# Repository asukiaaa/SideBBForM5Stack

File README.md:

# SideBBForM5Stack

An stack for M5Stack to use bread board easier.

# Where to buy

[SideBBForM5Stack - Switch Science](https://www.switch-science.com/catalog/4098/)

# License

MIT

# References

- [M5Stackの信号線をブレッドボードで扱いやすくするStackを作ってみた](https://asukiaaa.blogspot.com/2018/11/m5stacksidebb.html)
- [PartsandCircuits/M5Stack-3DPrintFiles](https://github.com/PartsandCircuits/M5Stack-3DPrintFiles)
- [DIY Mini Proto Board](http://forum.m5stack.com/topic/59/diy-mini-proto-board)

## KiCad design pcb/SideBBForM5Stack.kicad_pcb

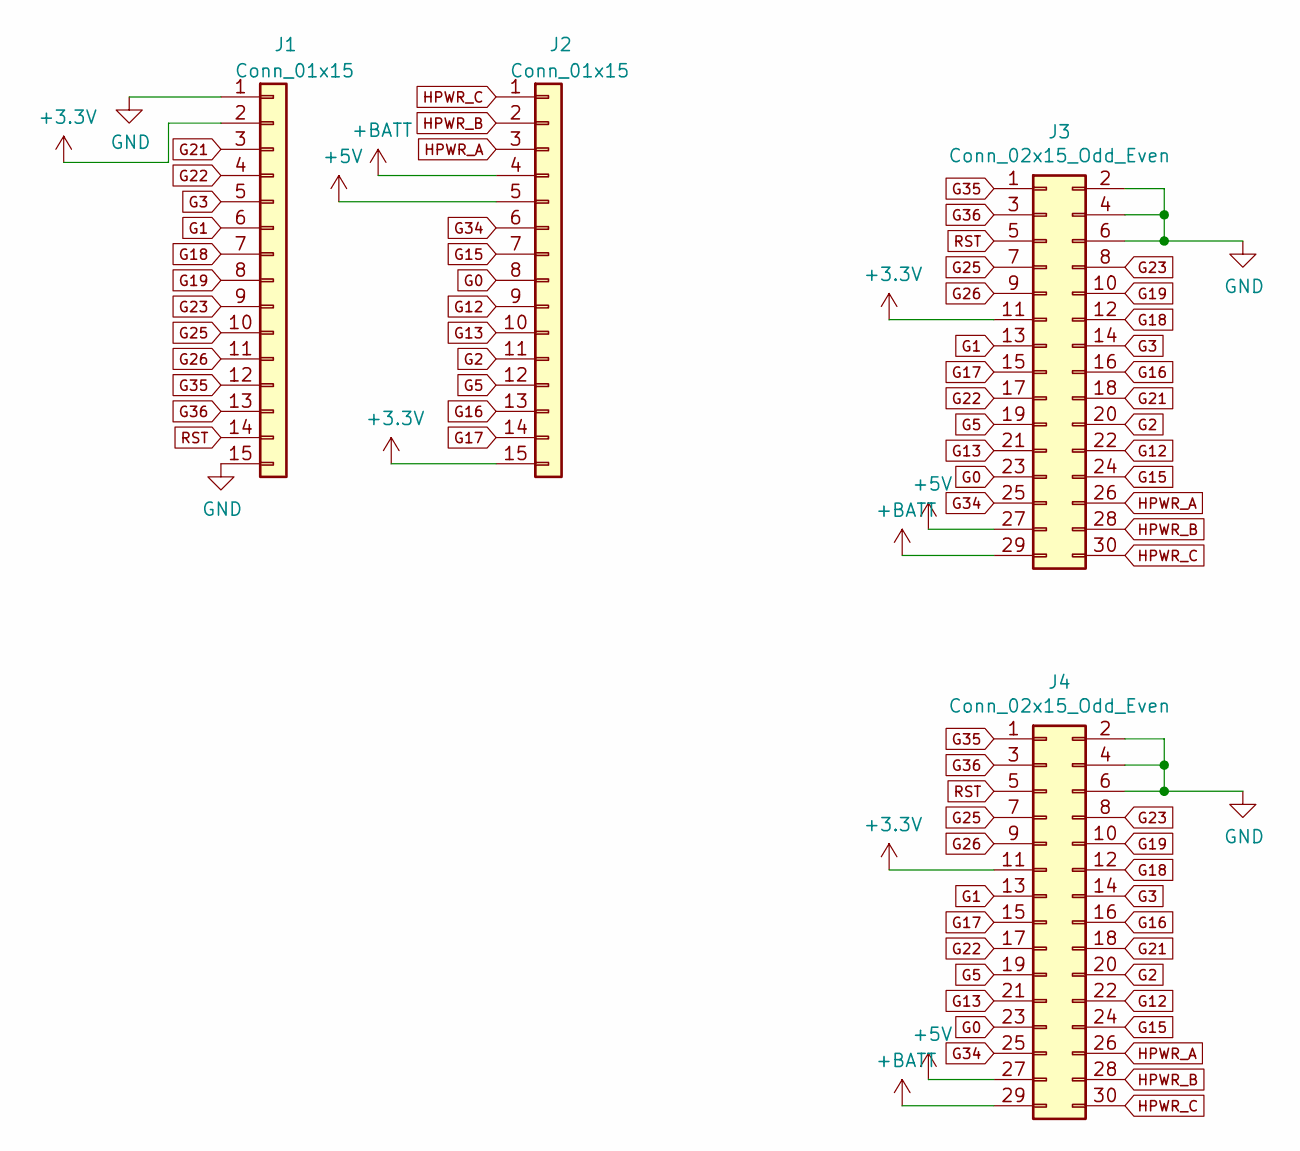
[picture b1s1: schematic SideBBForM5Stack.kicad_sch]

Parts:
J1, J2: Conn_01x15; PinSocket_1x15_P2.54mm_Vertical_without_silk
J3: Conn_02x15_Odd_Even; PinHeader_2x15_P2.54mm_M5Stack_SpacerPCB_pads
J4: Conn_02x15_Odd_Even; PinSocket_2x15_P2.54mm_Vertical_SMD_just_for_M5Stack_bottom

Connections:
+3V3: J1.2, J2.15, J3.11, J4.11
+5V: J2.5, J3.27, J4.27
+BATT: J2.4, J3.29, J4.29
G0: J2.8, J3.23, J4.23
G1: J1.6, J3.13, J4.13
G2: J2.11, J3.20, J4.20
G3: J1.5, J3.14, J4.14
G5: J2.12, J3.19, J4.19
G12: J2.9, J3.22, J4.22
G13: J2.10, J3.21, J4.21
G15: J2.7, J3.24, J4.24
G16: J2.13, J3.16, J4.16
G17: J2.14, J3.15, J4.15
G18: J1.7, J3.12, J4.12
G19: J1.8, J3.10, J4.10
G21: J1.3, J3.18, J4.18
G22: J1.4, J3.17, J4.17
G23: J1.9, J3.8, J4.8
G25: J1.10, J3.7, J4.7
G26: J1.11, J3.9, J4.9
G34: J2.6, J3.25, J4.25
G35: J1.12, J3.1, J4.1
G36: J1.13, J3.3, J4.3
GND: J1.1, J1.15, J3.2, J3.4, J3.6, J4.2, J4.4, J4.6
HPWR_A: J2.3, J3.26, J4.26
HPWR_B: J2.2, J3.28, J4.28
HPWR_C: J2.1, J3.30, J4.30
RST: J1.14, J3.5, J4.5

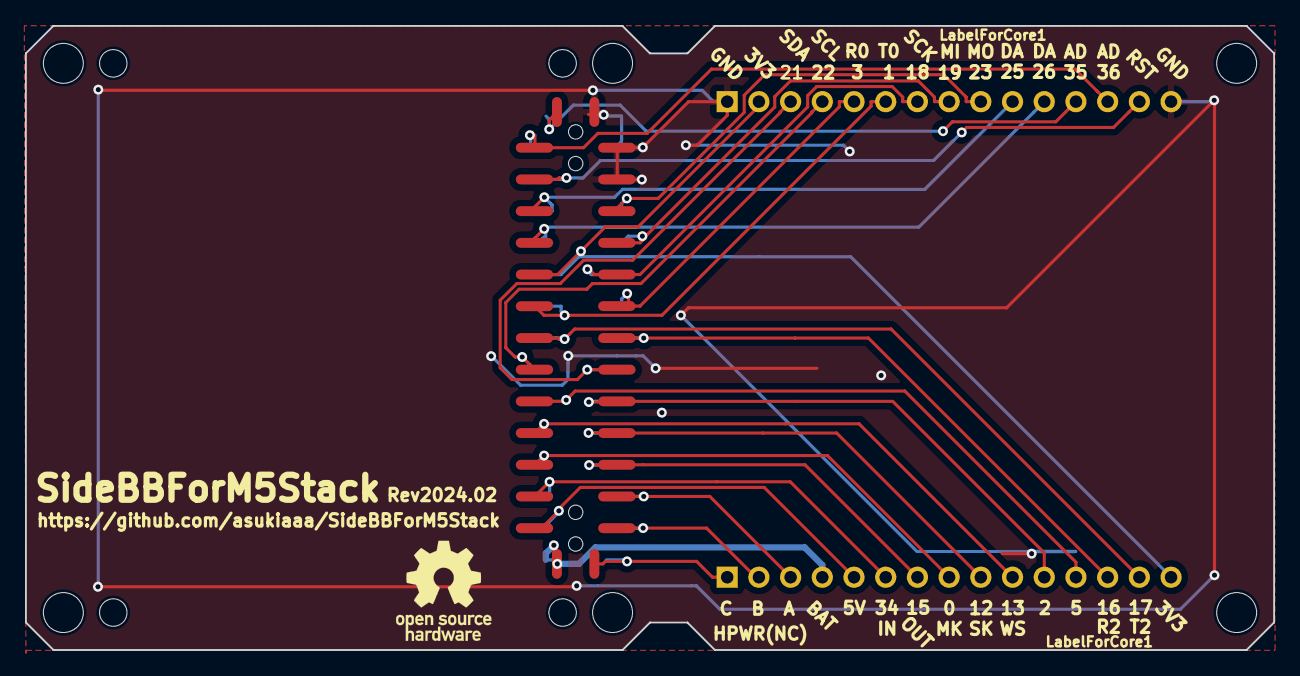
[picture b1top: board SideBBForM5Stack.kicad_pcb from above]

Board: 2 copper layers, 100.0 x 50.0 mm, 14 parts (1 on the bottom side), 28 nets.

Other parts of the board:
REF1, REF4, REF5, REF6, REF9, REF10: MountingHole_3.2mm_M3
REF2, REF3, REF7, REF8: MountingHole_2.2mm_M2

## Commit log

2018-06-16 Create schematic of M5StackSideBB
2018-06-18 Put components and holes as pcb
2018-06-18 Draw lines with using autorouter
2018-06-18 Update schema and put silk texts
2018-06-19 Create gerber files to order
2018-06-25 Create case in rough size
2018-06-26 Adjust size by referencing M5Stack
2018-06-26 Export stl
2018-06-28 Update sylk layout of names about pins
2018-06-29 Update size of case
2018-06-29 Update design of corner
2018-06-30 Make top corner thicker and put inside
2018-07-04 Change mounting hole size to M3 from M2.5
2018-07-05 Change top footprint
2018-07-06 Create spacer pcb roughly
2018-07-07 Update connecting hole position between pcb and spacer pcb
2018-07-07 Update revision and gerbers
2018-07-12 Change case height lower
2018-07-13 Change low length shorter and top hook smaller
2018-07-14 Export stl file
2018-07-17 Remove redundant reference on front fab
2018-07-18 Change space for breadborard narrower
2018-07-19 Change pinsocket on schema
2018-07-19 Correct pin assign for bottom socket
2018-07-20 Update component and its position on pcb
2018-07-20 Assign new footprint for spacer
2018-07-20 Update route of pcb
2018-07-21 Export gerber files to order rev 1.2
2018-07-24 Expand clearance of top and bottom for case
2018-07-26 Change back logo size larger
2018-07-27 Correct revision of spacer_pcb
2018-07-30 Add explanatio about M5StackBB
2018-10-05 Change innner size smaller
2018-10-21 Add license info
2018-11-09 Update design for production
2018-11-09 Change pad position as Rev 2018.11
2018-11-17 Change bottom space to 1.0mm from 1.2mm
2018-11-17 Change bottom length to 6.2mm from 6.5mm
2018-11-17 Add space to remove for bottom area
2018-11-17 Update stl
2018-11-17 Update poition of a space to remove
2018-11-17 Change space of bottom space to 1.1mm from 1.0mm
2018-11-17 Update stl file
2018-11-17 Change bottom length 0.6mm longer
2018-11-18 Change position of a space to remove as y9.5mm from y9.0mm
2018-12-02 Add images on readme
2018-12-02 Add link of product page of switch swience on readme
2018-12-02 Add 4 holes to detect position of spacer_pcb
2018-12-02 Add open source hardware logo
2018-12-02 Assign footprint of pin socket without silk
2018-12-02 Change GND via position arround G2
2018-12-02 Update gerber files
2018-12-16 Correct UART number for G1 and G3
2018-12-21 Use 14 pins headers
2018-12-21 Remove redundant top pad
2018-12-21 Remove redundant info from spacer pcb
2019-01-20 Add requirements for pcba
2019-01-20 Craete directory of case for zotrax m200plus
2019-01-20 Add narrow inner size case
2019-03-09 Remove redundant wire
2019-03-14 Change footprint for top pad without THT holes
2019-03-14 Update gerbers for main pcb
2019-03-16 Update bom
2019-03-16 Update requirements
2019-05-03 Apply smaller pads for top and bottom
2019-05-05 Change link for breadboard on bom.csv
2019-05-05 Add bottom pads for spacer PCB
2019-05-12 Correct y center position for smd pads
2019-05-29 Add a link for my blog post as reference
2019-08-21 Remove redundant footprint
2019-08-21 Add fp-info-cache to gitignore for KiCad5
2019-08-21 Update as narrow long style for pcb to spacer pads
2019-08-21 Remove gerbers from git
2019-08-21 Add directory for export gerber to .gitignore
2019-11-02 Update spacer pad style
2019-11-03 Rename project name to SideBBForM5Stack from M5StackSideBB
2019-11-04 Remove redundant project file
2019-12-08 Change hole size on spacer pcb larger
2020-02-01 Update size of pads
2021-03-23 Use 1x15 pinsocket as Rev2021.03
2021-03-28 Add label to mension that the labels for Core1
2021-05-17 Change text position for LabelForCore1
2021-10-10 Add label image for core2
2021-10-10 Correct image size for label tiles
2022-02-22 Update bom to use new header
2022-02-23 Update main pcb for KiCad6
2022-02-23 Update filling with using kicad6
2023-02-01 Update requirements and bom
2023-02-07 Update filling of main pcb
2023-03-18 Correct revision on back silks
2023-03-26 Add tiles for core_s3
2023-04-11 Add tiles for core s3
2023-04-11 Remove not used tiles image
2023-04-11 Add a tile image for core s3
2023-04-11 Remove extension of source file to create tiles
2023-09-26 Update for KiCad7
2023-12-27 Add holes for socket to spacer pcb
2023-12-27 Move header and socket position 0.03mm inside as rev2024.01
2024-01-17 Expand hole size to 1.0 from 0.9mm
2024-06-11 Update sticker data for core s3
2024-06-11 Expanded size of holes for mbus connectors
